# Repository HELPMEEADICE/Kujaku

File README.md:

# Kujaku（孔雀）

Kujaku 是一套用于孔雀造型灯光装置的开源硬件与固件设计，包含多路 PWM 主控板、3S 18650 电池与充电板、外壳模型和 ESP32-C3 固件。仓库中的历史文件沿用 Peacock 命名。

## 项目内容

- [主板 V2.1](PeacockMainV2_1/PeacockMainV2_1-Design.md)：KiCad 原理图、PCB、制造文件与设计记录，提供 12 路 PWM 和电流采样。
- [电池板 A2](PeacockBattery/A2/PeacockBattery-Design.md)：3S 电池、充电与握把接口设计，包含制造资料。
- [ESP32-C3 固件](firmware/peacock-esp32c3/README.md)：Rust 固件，包含灯效、音频、BLE 和电源管理；编译、烧录及接口说明见其 README。
- [外壳](PeacockEnclosure/)与[装配效果图](renders/)：DWG、STL、模型导出和渲染图。
- [主板 V2](PeacockMainV2/PeacockMainV2-Design.md)、[电池板 A1](PeacockBattery/PeacockBattery-Design.md)及仓库根目录的 KiCad 工程为历史版本，请按相应版本的文档使用。

## 开始使用

使用 KiCad 10 打开相应目录中的 `.kicad_pro`，并参考各设计记录中的接口、物料和制造说明。外壳模型位于 `PeacockEnclosure/`。固件的工具链、构建和烧录步骤详见[固件说明](firmware/peacock-esp32c3/README.md)。

**项目仍需实物验证。** ERC/DRC 结果不代表整机通过验证；电池接触、充放电保护、温升、装壳及接口兼容性等须按对应版本的设计记录完成验证。固件中的 PY32 采样从机协议仍是提案，仓库未提供该从机固件。制作或上电前请先阅读相关设计记录。

## 许可

本项目原创固件和其他软件代码采用 [GNU Affero General Public License v3.0](LICENSE)（AGPL-3.0-only）；原创硬件设计、外壳、渲染图及文档采用 [Creative Commons Attribution-ShareAlike 4.0 International](LICENSE-CC-BY-SA-4.0)（CC BY-SA 4.0）。使用设计资料时请署名 Kujaku 项目及相关贡献者，并遵守相同方式共享要求。

第三方材料及依赖仍遵循各自的许可和声明；例如 ESP32 模型相关许可见 [Espressif 许可文件](PeacockMainV2_1/Espressif-LICENSE.md)。上述许可不改变第三方权利。

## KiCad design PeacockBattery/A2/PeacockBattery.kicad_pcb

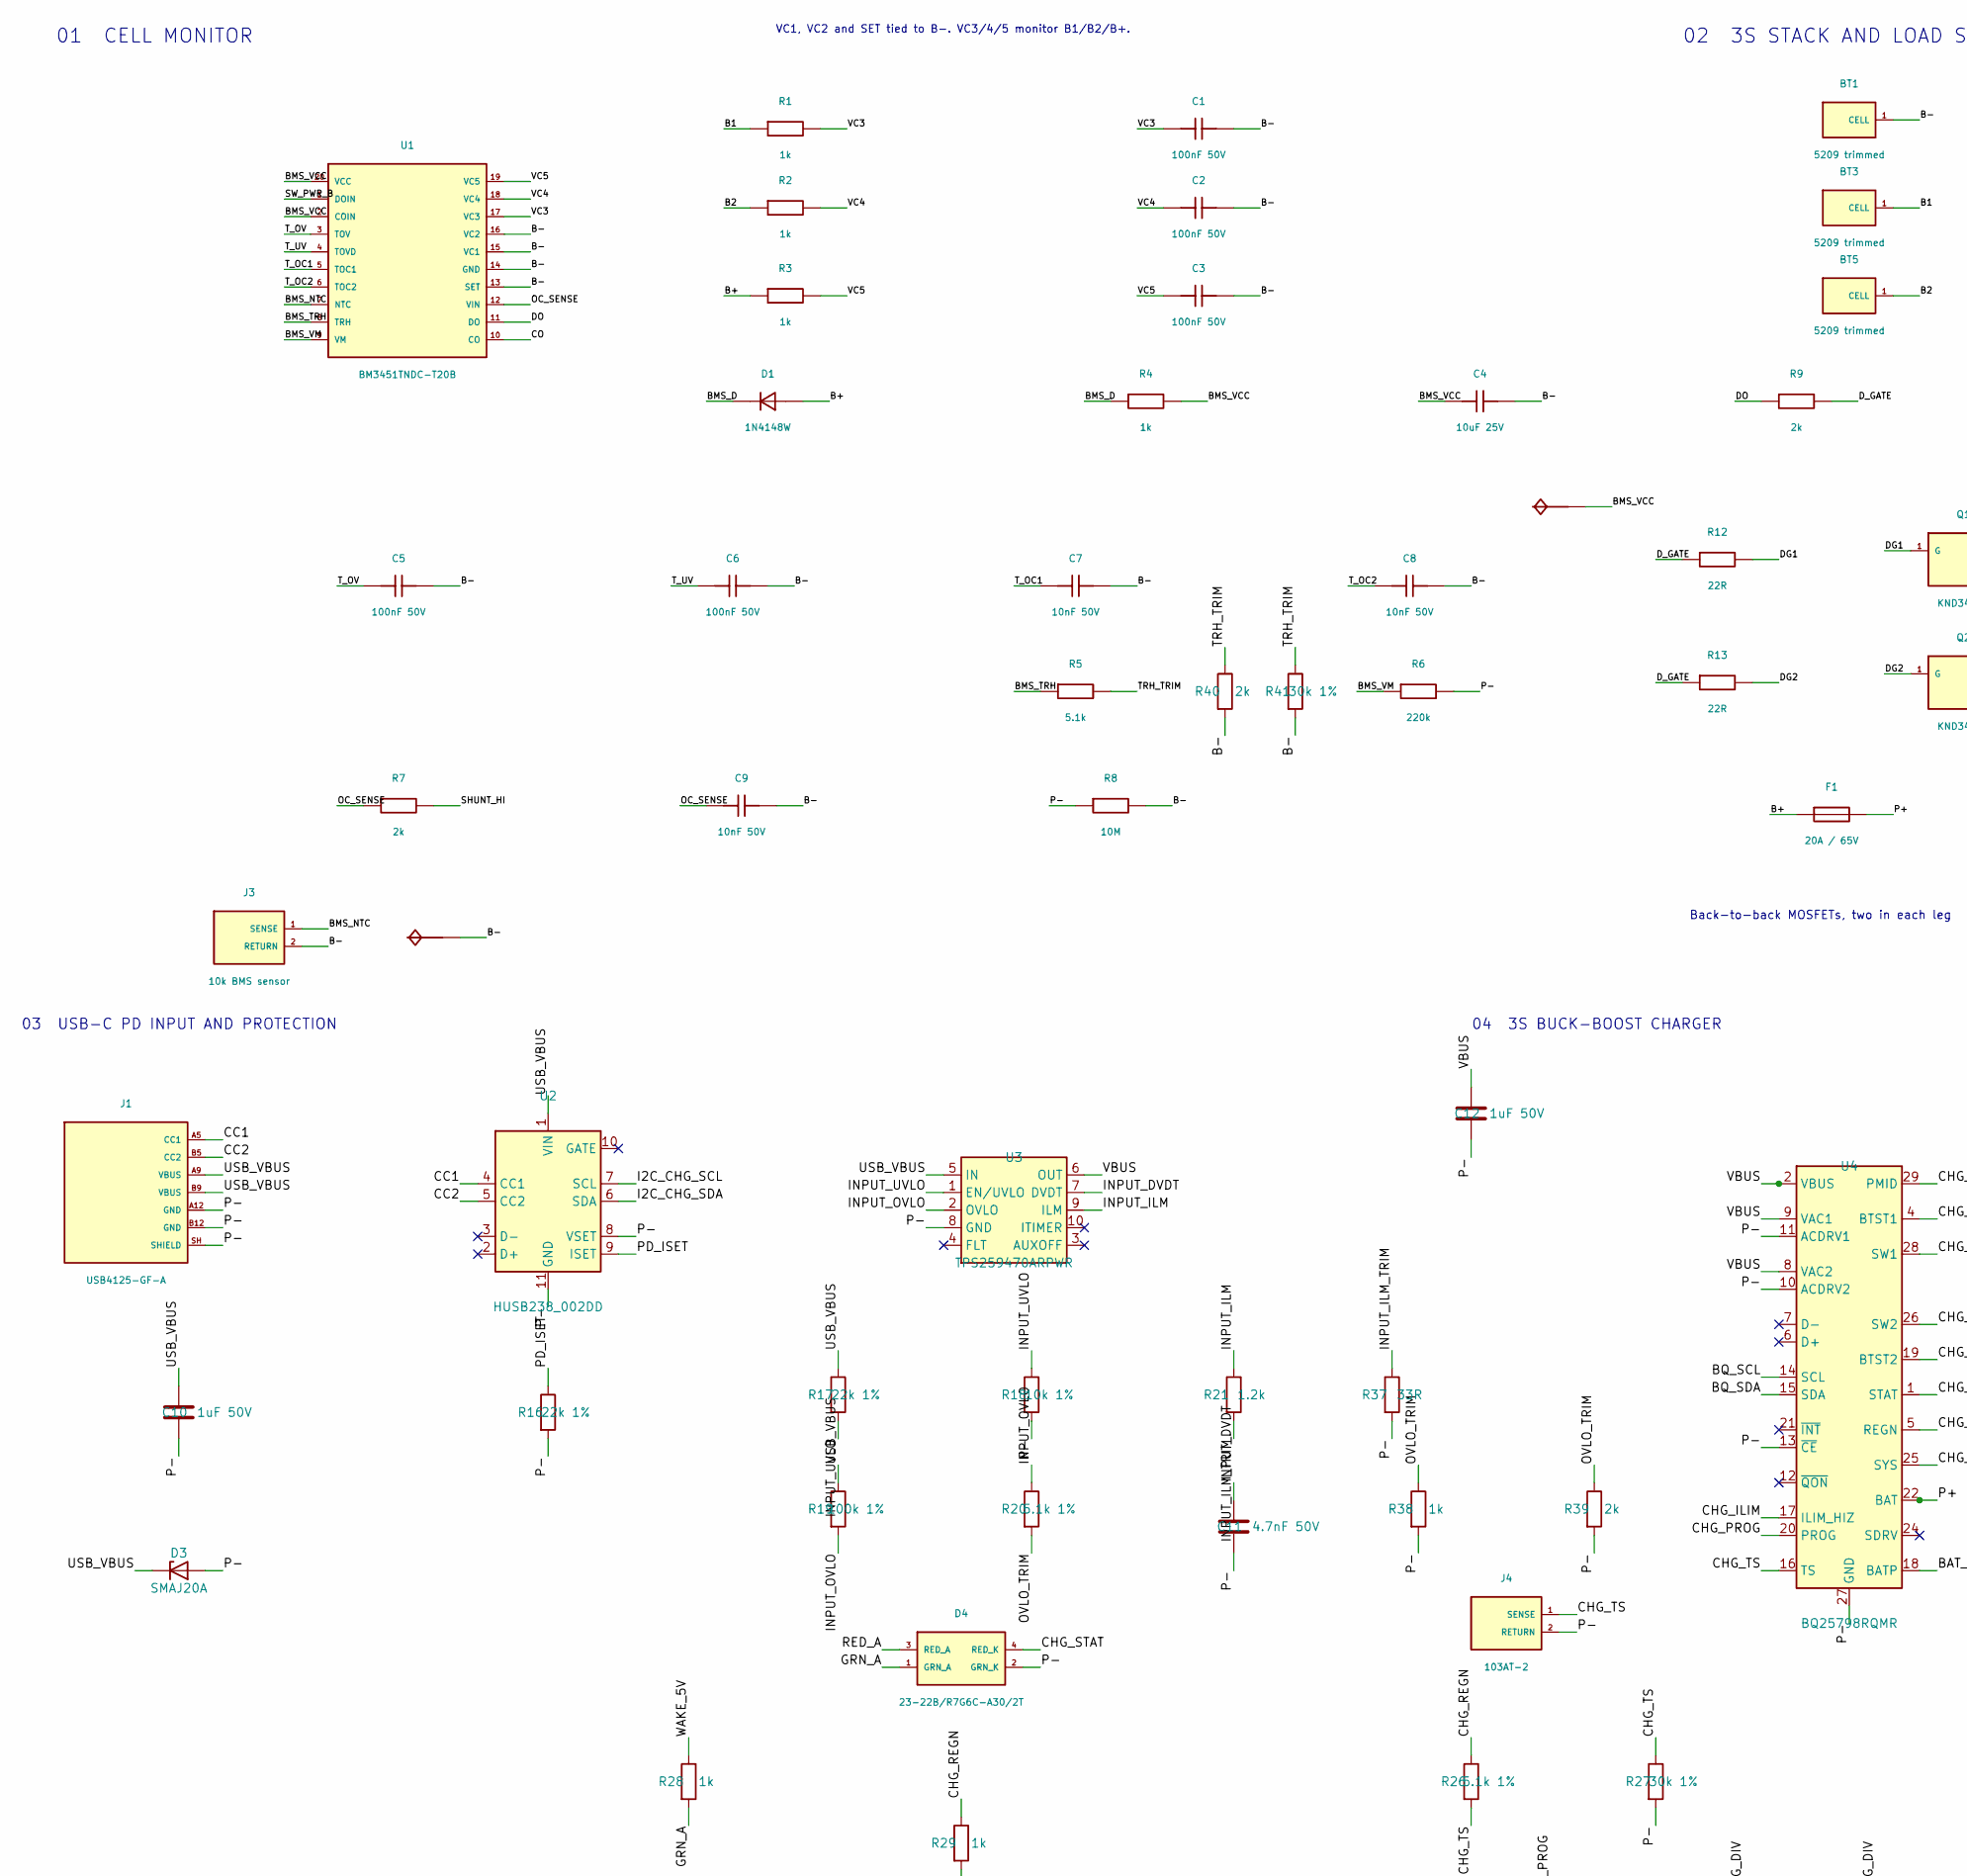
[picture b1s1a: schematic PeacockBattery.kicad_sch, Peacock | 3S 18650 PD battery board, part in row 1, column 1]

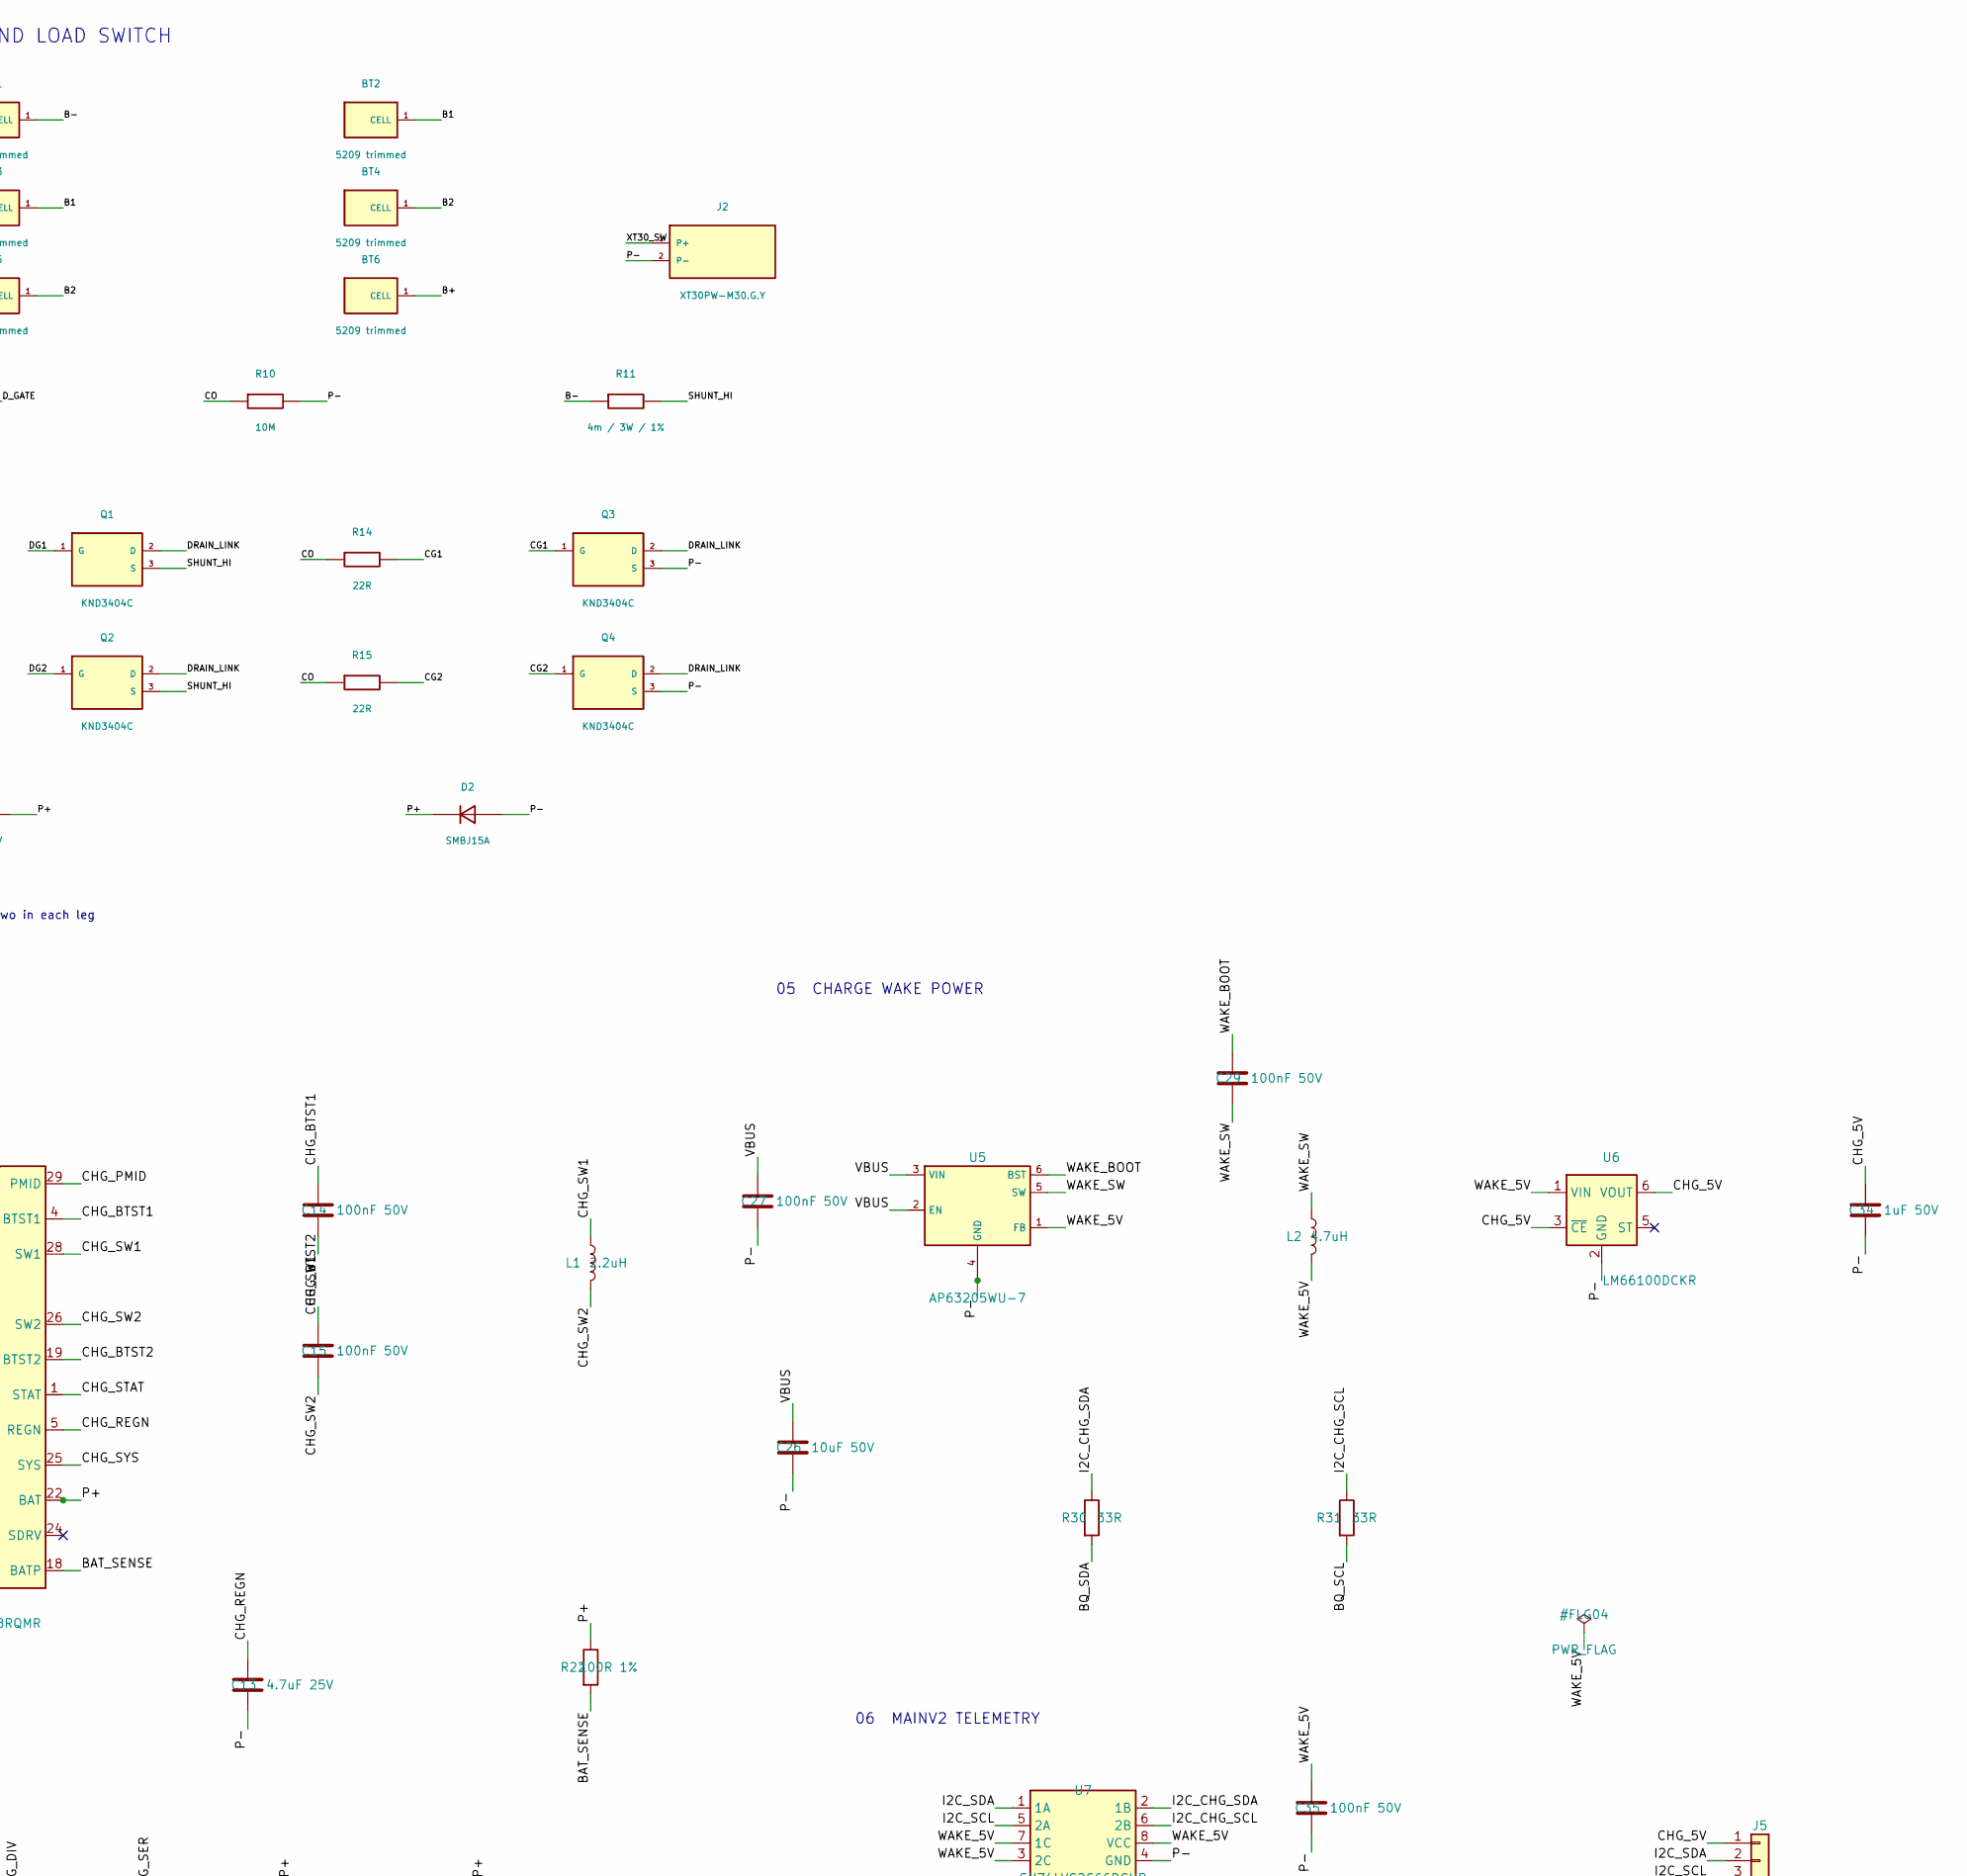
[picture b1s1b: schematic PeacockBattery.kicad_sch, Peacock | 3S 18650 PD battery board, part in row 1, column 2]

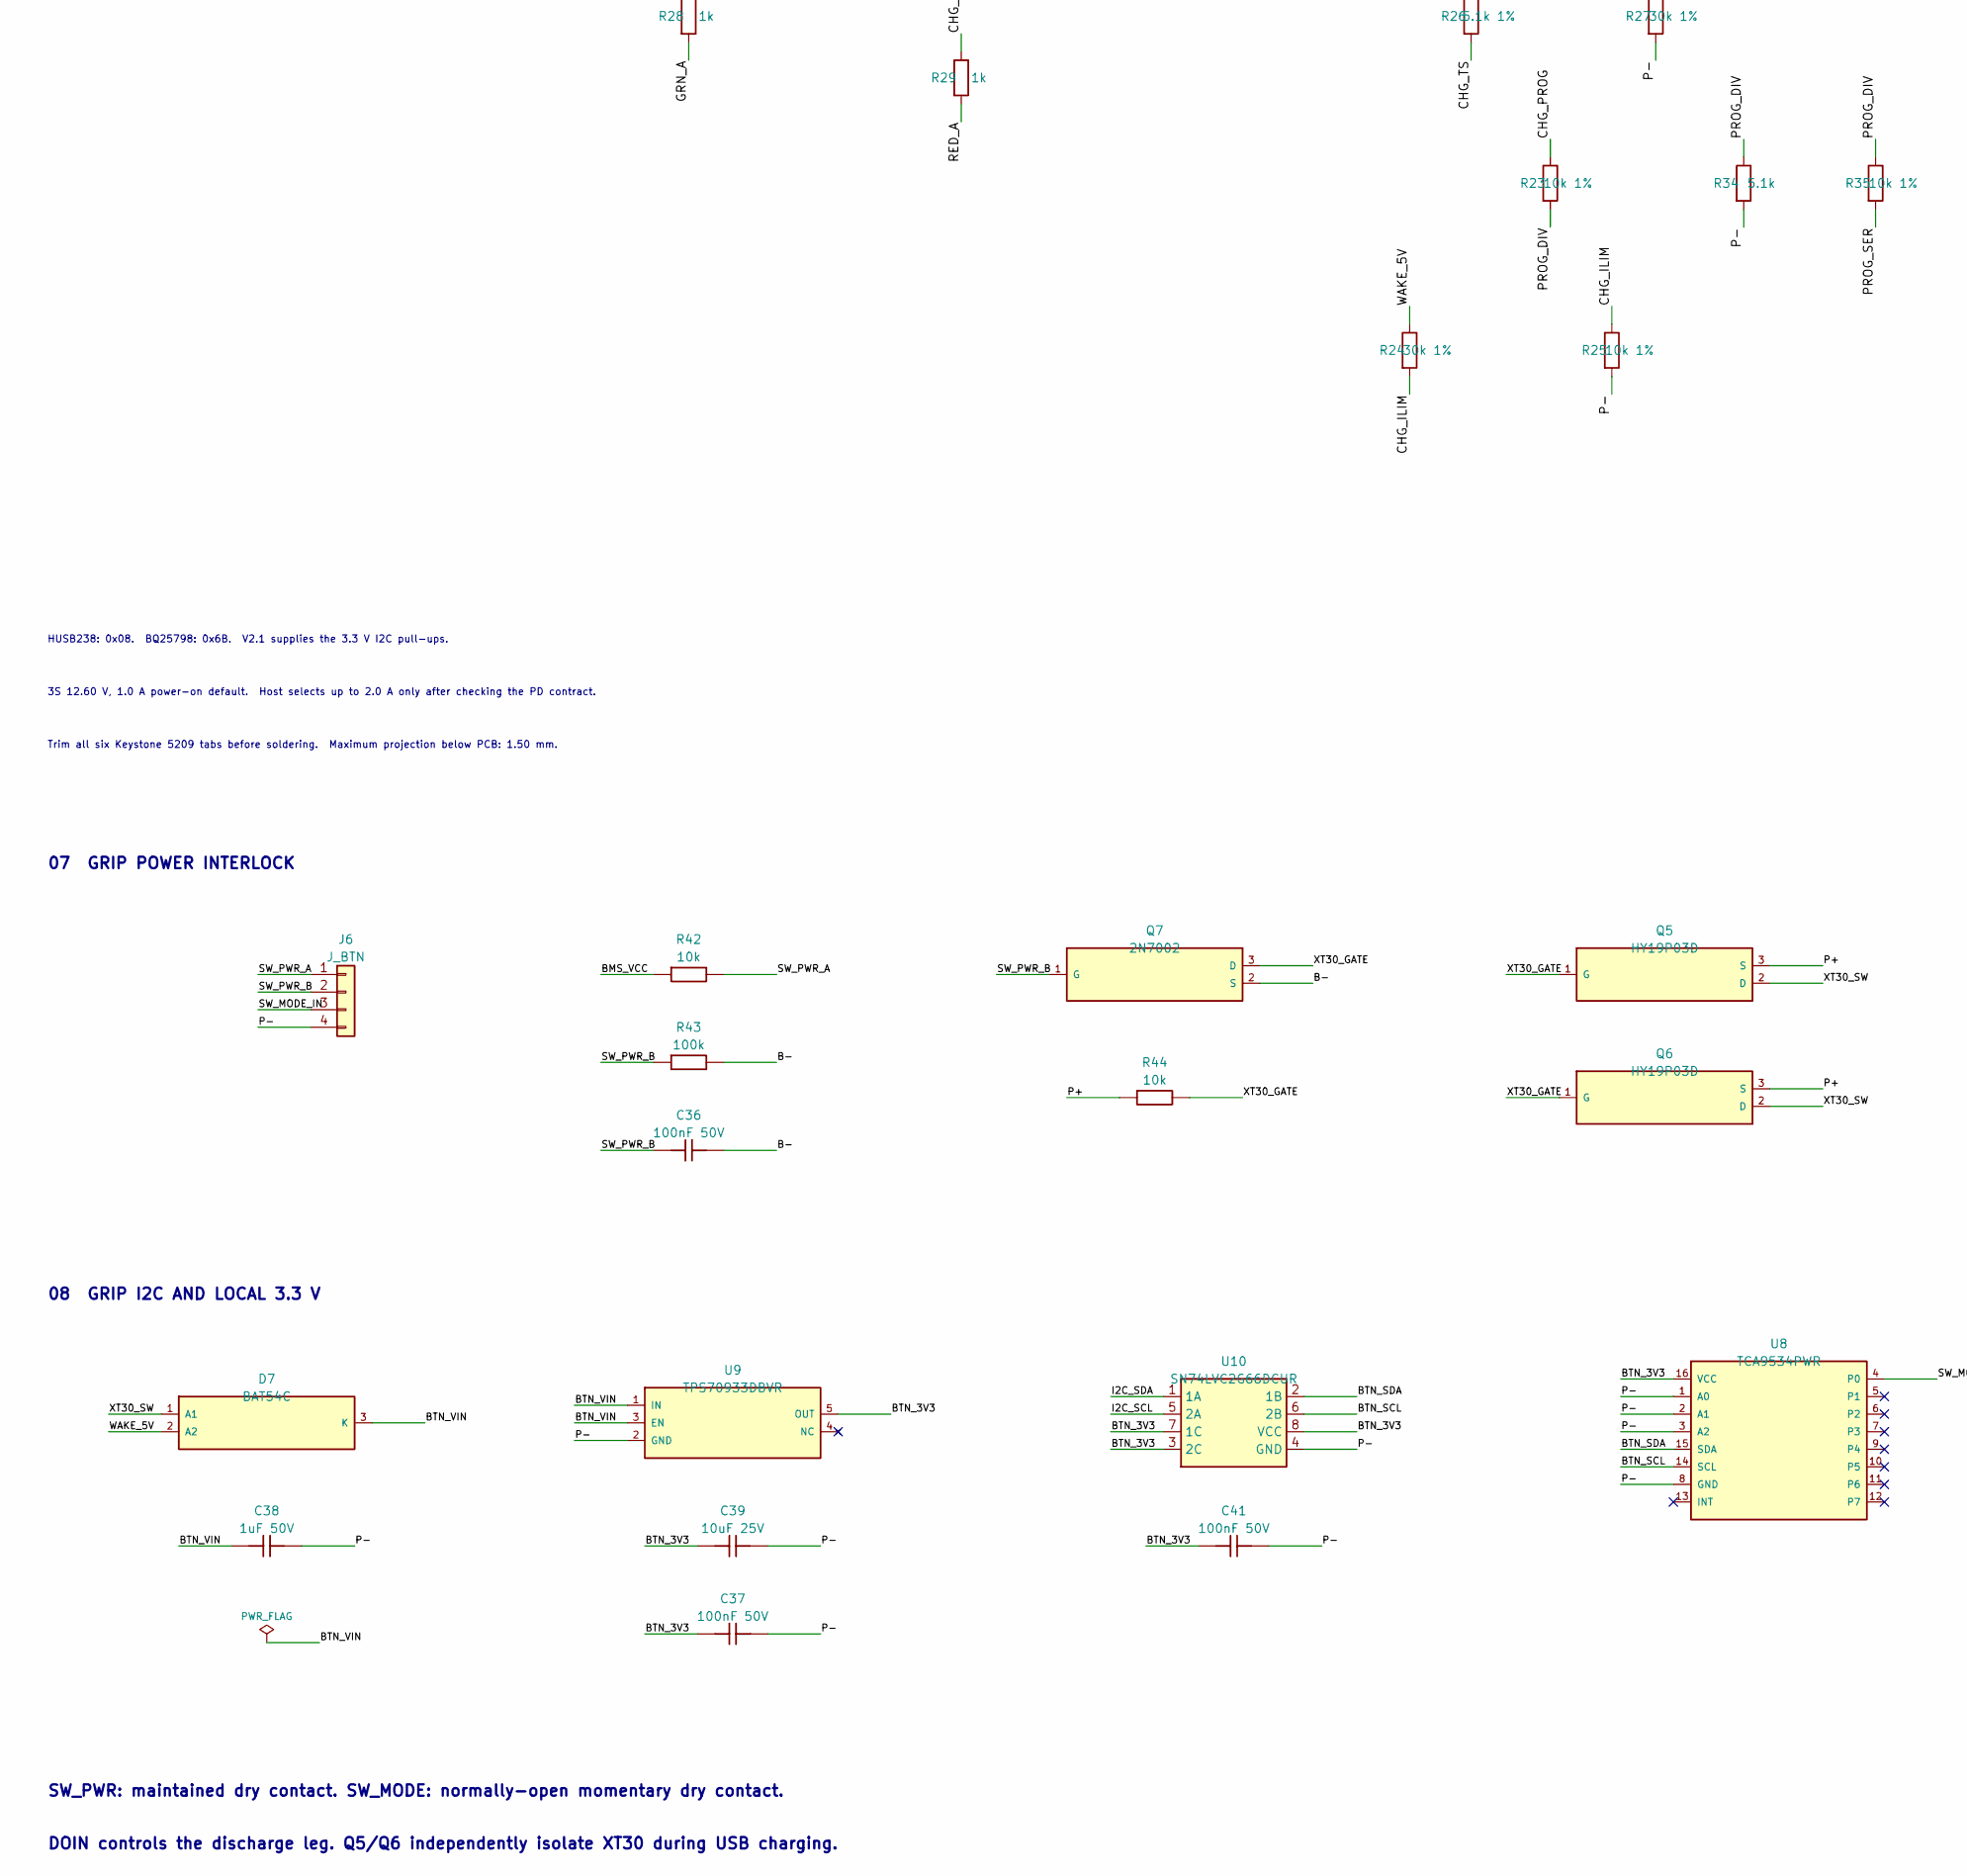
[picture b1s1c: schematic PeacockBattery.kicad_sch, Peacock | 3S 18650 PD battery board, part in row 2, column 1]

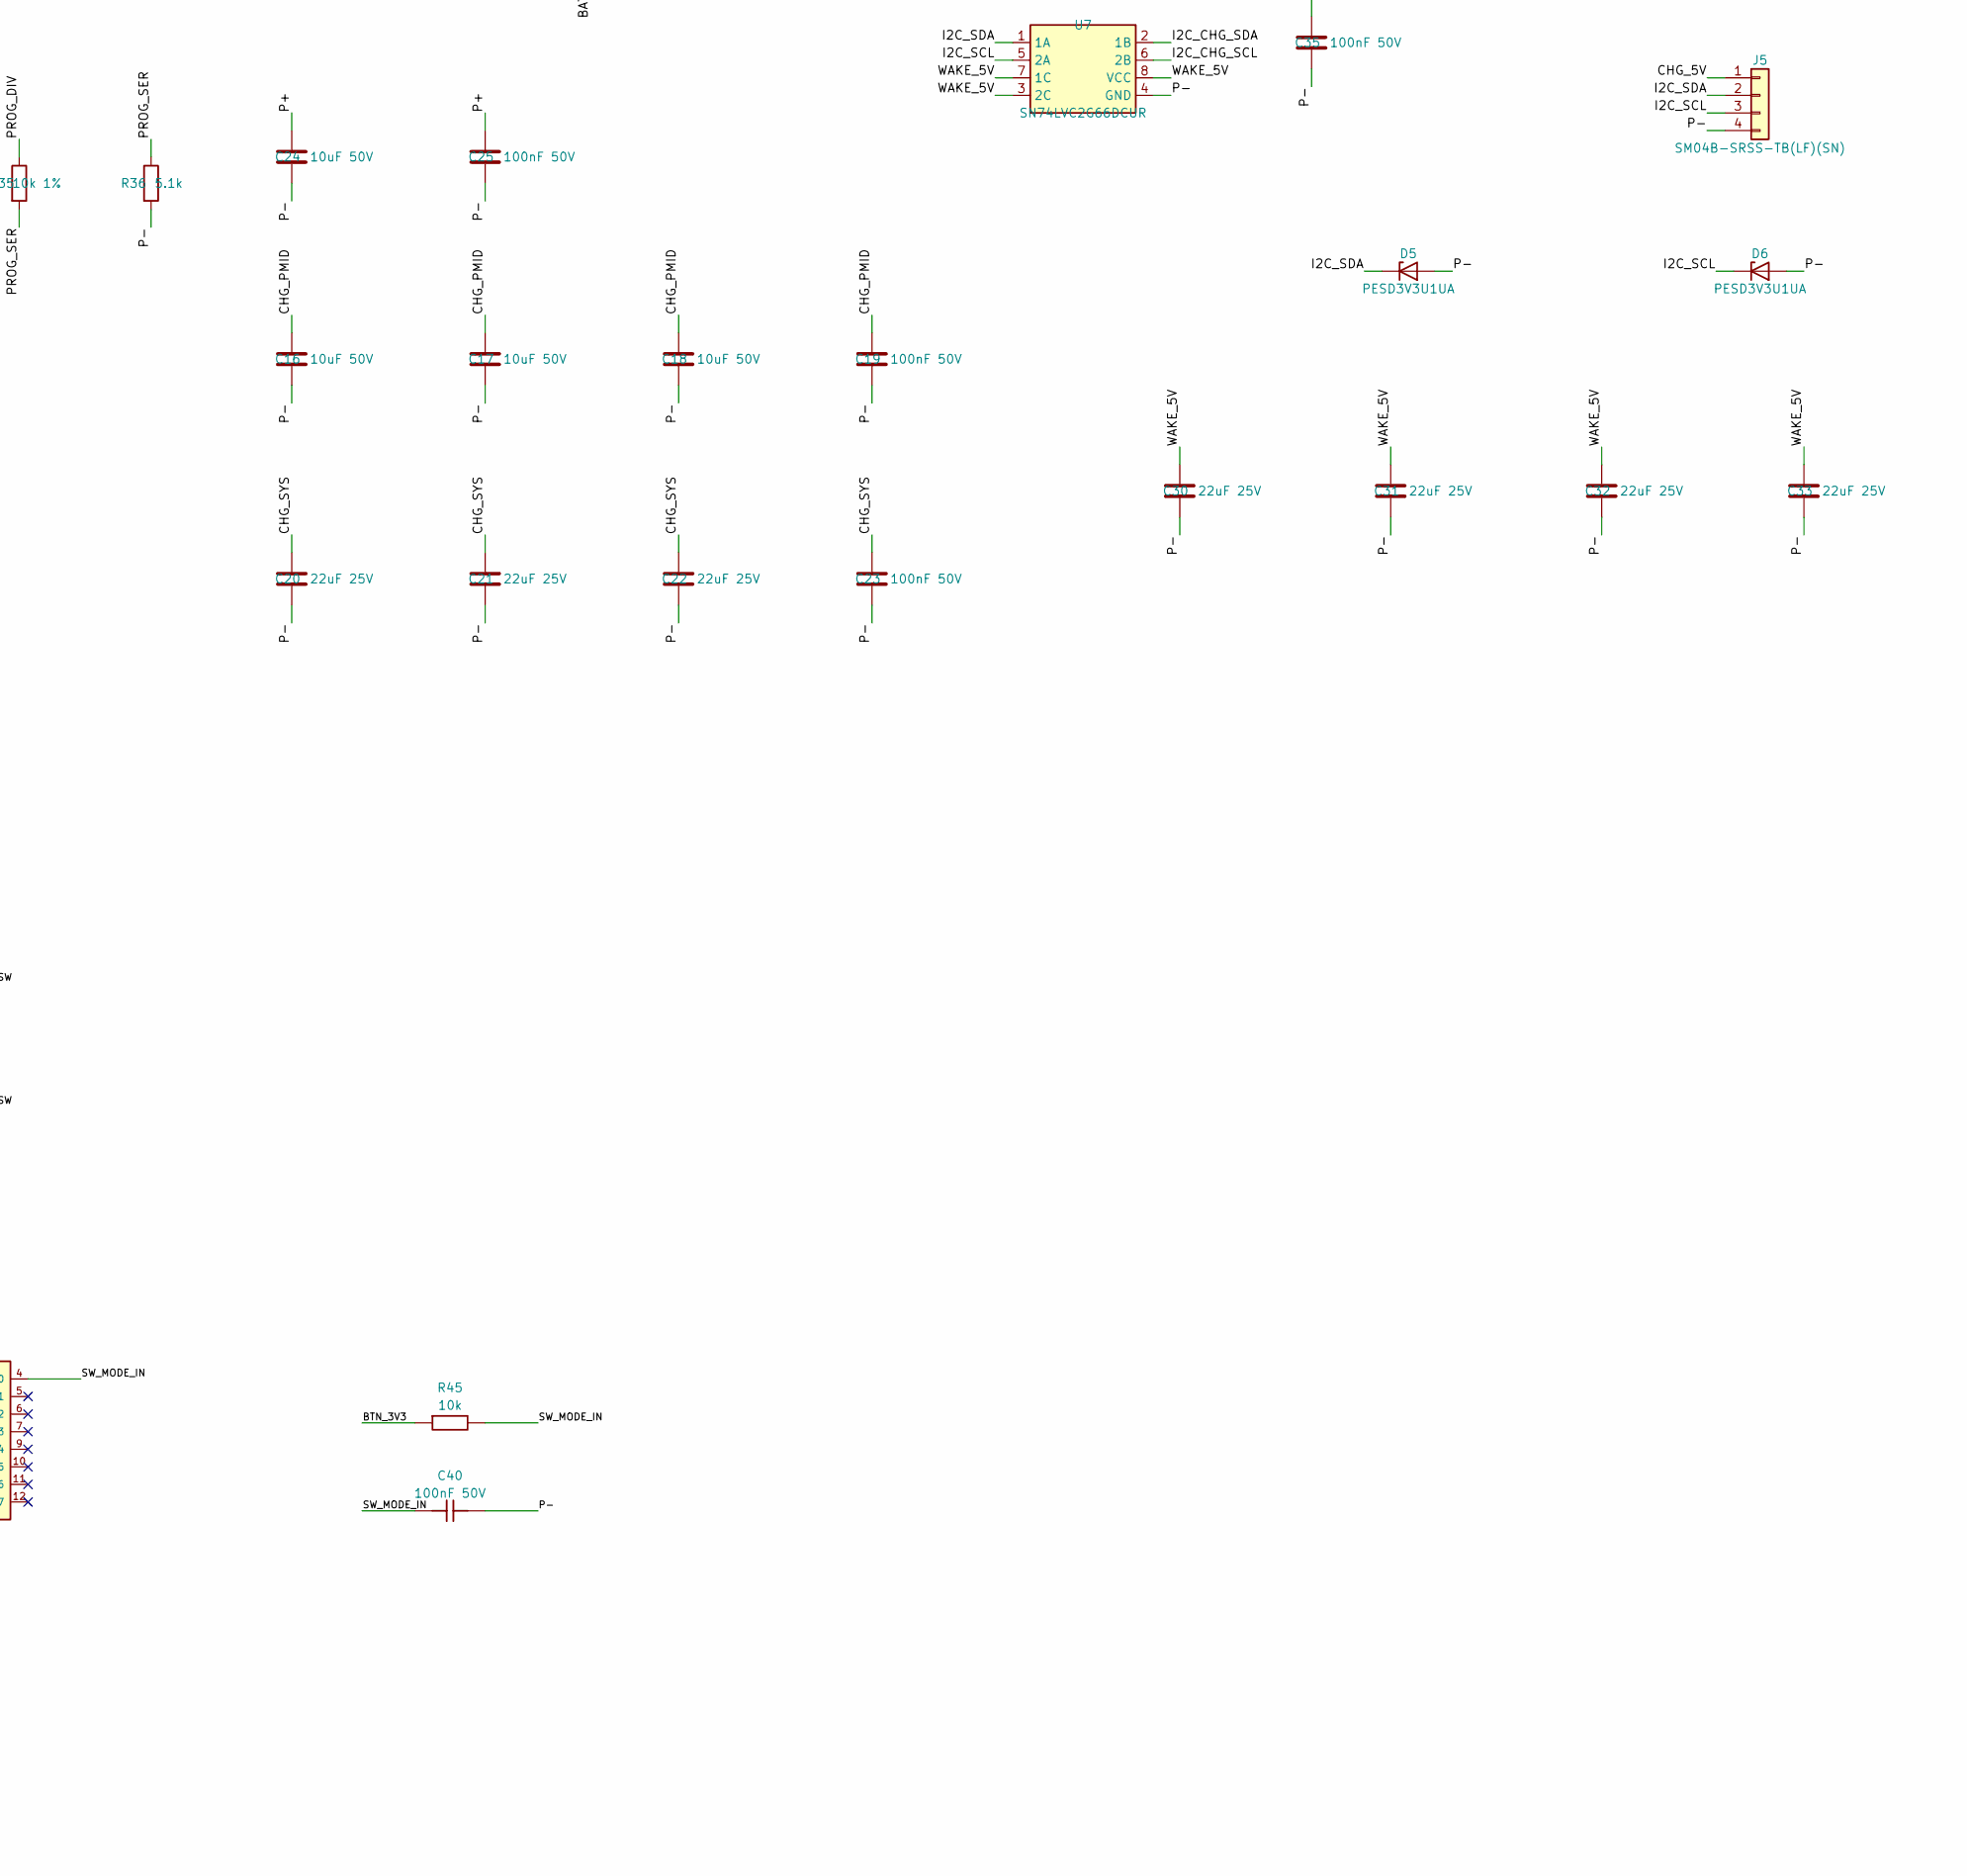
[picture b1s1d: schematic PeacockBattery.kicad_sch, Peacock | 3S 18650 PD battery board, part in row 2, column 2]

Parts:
BT1, BT2, BT3, BT4, BT5, BT6: 5209 trimmed; Keystone_5209_Trimmed; MPN TBD
C1, C2, C3, C5, C6, C14, C15, C19, C23, C25, C27, C29, C35, C36, C37, C40, C41: 100nF 50V; C_0603_1608Metric; MPN CC0603KRX7R9BB104; LCSC C14663
C4, C39: 10uF 25V; C_0805_2012Metric; MPN CL21A106KAYNNNE; LCSC C15850
C7, C8, C9: 10nF 50V; C_0603_1608Metric; MPN 0603B103K500NT; LCSC C57112
C10, C12, C34, C38: 1uF 50V; C_0603_1608Metric; MPN CL10A105KB8NNNC; LCSC C15849
C11: 4.7nF 50V; C_0603_1608Metric; MPN 0603B472K500NT; LCSC C53987
C13: 4.7uF 25V; C_0805_2012Metric; MPN CL21A475KAQNNNE; LCSC C1779
C16, C17, C18, C24, C26: 10uF 50V; C_1206_3216Metric; MPN CL31A106KBHNNNE; LCSC C13585
C20, C21, C22: 22uF 25V; C_1206_3216Metric; MPN CL31A226KAHNNNE; LCSC C12891
C30, C31, C32, C33: 22uF 25V; C_0805_2012Metric; MPN CL21A226MAQNNNE; LCSC C45783
D1: 1N4148W; D_SOD-123; MPN 1N4148W; LCSC C81598
D2: SMBJ15A; D_SMB; MPN SMBJ15A; LCSC C19077569
D3: SMAJ20A; D_SMA; MPN SMAJ20A; LCSC C41376408
D4: 23-22B/R7G6C-A30/2T; LED_Everlight_23-22B_Reverse; MPN 23-22B/R7G6C-A30/2T; LCSC C424084
D5, D6: PESD3V3U1UA; D_SOD-323; MPN PESD3V3U1UA,115; LCSC C403915
D7: BAT54C; SOT-23; MPN BAT54C; LCSC C2135
F1: 20A / 65V; Fuse_Littelfuse-NANO2-451_453; MPN 0451020.MRL; LCSC C178980
J1: USB4125-GF-A; USB4125_HandAssembly; MPN USB4125-GF-A; LCSC C3151650
J2: XT30PW-M30.G.Y; XT30PW-M_Edge; MPN XT30PW-M30.G.Y; LCSC C431092
J3: 10k BMS sensor; SolderWire-0.15sqmm_1x02_P4mm_D0.5mm_OD1.5mm; MPN 10k NTC, insulated leads
J4: 103AT-2; SolderWire-0.15sqmm_1x02_P4mm_D0.5mm_OD1.5mm; MPN 103AT-2
J5: SM04B-SRSS-TB(LF)(SN); JST_SH_SM04B_HandAssembly; MPN SM04B-SRSS-TB(LF)(SN); LCSC C160404
J6: J_BTN; Grip_1x04_SolderPads; MPN Wire-to-pad; LCSC N/A
L1: 2.2uH; L_APV_APH0530C; MPN APH0530C-2R2M-TCD5; LCSC C50326270
L2: 4.7uH; L_YJYCOIN_YSPI0730; MPN YSPI0730-4R7M; LCSC C351117
Q1, Q2, Q3, Q4: KND3404C; TO-252-2; MPN KND3404C; LCSC C455981
Q5, Q6: HY19P03D; TO-252-2; MPN HY19P03D; LCSC C122492
Q7: 2N7002; SOT-23; MPN 2N7002; LCSC C8545
R1, R2, R3, R4, R28, R29, R38: 1k; R_0603_1608Metric; MPN 0603WAF1001T5E; LCSC C21190
R5, R34, R36: 5.1k; R_0603_1608Metric; MPN 0603WAF5101T5E; LCSC C23186
R6: 220k; R_0603_1608Metric; MPN 0603WAF2203T5E; LCSC C22961
R7, R9, R39, R40: 2k; R_0603_1608Metric; MPN 0603WAF2001T5E; LCSC C22975
R8, R10: 10M; R_0603_1608Metric; MPN 0603WAF1005T5E; LCSC C7250
R11: 4m / 3W / 1%; WSLP2512_4m; MPN WSLP25124L000FEA; LCSC C2091033
R12, R13, R14, R15: 22R; R_0603_1608Metric; MPN 0603WAF220JT5E; LCSC C23345
R16, R17: 22k 1%; R_0603_1608Metric; MPN 0603WAF2202T5E; LCSC C31850
R18, R23, R25, R35: 10k 1%; R_0603_1608Metric; MPN 0603WAF1002T5E; LCSC C25804
R19: 100k 1%; R_0603_1608Metric; MPN 0603WAF1003T5E; LCSC C25803
R20, R26: 5.1k 1%; R_0603_1608Metric; MPN 0603WAF5101T5E; LCSC C23186
R21: 1.2k; R_0603_1608Metric; MPN 0603WAF1201T5E; LCSC C22765
R22: 100R 1%; R_0603_1608Metric; MPN 0603WAF1000T5E; LCSC C22775
R24, R27, R41: 30k 1%; R_0603_1608Metric; MPN 0603WAF3002T5E; LCSC C22984
R30, R31, R37: 33R; R_0603_1608Metric; MPN 0603WAF330JT5E; LCSC C23140
R42, R44, R45: 10k; R_0603_1608Metric; MPN 0603WAF1002T5E; LCSC C25804
R43: 100k; R_0603_1608Metric; MPN 0603WAF1003T5E; LCSC C25803
U1: BM3451TNDC-T20B; TSSOP-20_4.4x6.5mm_P0.65mm; MPN BM3451TNDC-T20B; LCSC C2686222
U2: HUSB238_002DD; WDFN-10-1EP_3x3mm_P0.5mm_EP1.8x2.5mm; MPN HUSB238_002DD; LCSC C7471904
U3: TPS259470ARPWR; TI_RPW0010A; MPN TPS259470ARPWR; LCSC C3662799
U4: BQ25798RQMR; Texas_RQM0029A_VQFN-29_4x4mm_P0.4mm; MPN BQ25798RQMR; LCSC C2876593
U5: AP63205WU-7; TSOT-23-6; MPN AP63205WU-7; LCSC C2071056
U6: LM66100DCKR; SOT-363_SC-70-6; MPN LM66100DCKR; LCSC C2869734
U7, U10: SN74LVC2G66DCUR; VSSOP-8_2.3x2mm_P0.5mm; MPN SN74LVC2G66DCUR; LCSC C181970
U8: TCA9534PWR; TSSOP-16_4.4x5mm_P0.65mm; MPN TCA9534PWR; LCSC C783615
U9: TPS70933DBVR; SOT-23-5; MPN TPS70933DBVR; LCSC C89347

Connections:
/B1: BT2.1, BT3.1, R1.1
/B2: BT4.1, BT5.1, R2.1
/B+: BT6.1, D1.2, F1.1, R3.1
/B-: BT1.1, C1.2, C2.2, C3.2, C4.2, C5.2, C6.2, C7.2, C8.2, C9.2, C36.2, J3.2 (RETURN), Q7.2 (S), R8.2, R11.1, R40.2, R41.2, R43.2, U1.13 (SET), U1.14 (GND), U1.15 (VC1), U1.16 (VC2)
/BAT_SENSE: R22.2, U4.18 (BATP)
/BMS_D: D1.1, R4.1
/BMS_NTC: J3.1 (SENSE), U1.7 (NTC)
/BMS_TRH: R5.1, U1.8 (TRH)
/BMS_VCC: C4.1, R4.2, R42.1, U1.2 (COIN), U1.20 (VCC)
/BMS_VM: R6.1, U1.9 (VM)
/BQ_SCL: R31.2, U4.14 (SCL)
/BQ_SDA: R30.2, U4.15 (SDA)
/BTN_3V3: C37.1, C39.1, C41.1, R45.1, U8.16 (VCC), U9.5 (OUT), U10.3 (2C), U10.7 (1C), U10.8 (VCC)
/BTN_SCL: U8.14 (SCL), U10.6 (2B)
/BTN_SDA: U8.15 (SDA), U10.2 (1B)
/BTN_VIN: C38.1, D7.3 (K), U9.1 (IN), U9.3 (EN)
/CC1: J1.A5 (CC1), U2.4 (CC1)
/CC2: J1.B5 (CC2), U2.5 (CC2)
/CG1: Q3.1 (G), R14.2
/CG2: Q4.1 (G), R15.2
/CHG_5V: C34.1, J5.1, U6.3 (~CE), U6.6 (VOUT)
/CHG_BTST1: C14.1, U4.4 (BTST1)
/CHG_BTST2: C15.1, U4.19 (BTST2)
/CHG_ILIM: R24.2, R25.1, U4.17 (ILIM_HIZ)
/CHG_PMID: C16.1, C17.1, C18.1, C19.1, U4.29 (PMID)
/CHG_PROG: R23.1, U4.20 (PROG)
/CHG_REGN: C13.1, R26.1, R29.1, U4.5 (REGN)
/CHG_STAT: D4.4 (RED_K), U4.1 (STAT)
/CHG_SW1: C14.2, L1.1, U4.28 (SW1)
/CHG_SW2: C15.2, L1.2, U4.26 (SW2)
/CHG_SYS: C20.1, C21.1, C22.1, C23.1, U4.25 (SYS)
/CHG_TS: J4.1 (SENSE), R26.2, R27.1, U4.16 (TS)
/CO: R10.1, R14.1, R15.1, U1.10 (CO)
/DG1: Q1.1 (G), R12.2
/DG2: Q2.1 (G), R13.2
/DO: R9.1, U1.11 (DO)
/DRAIN_LINK: Q1.2 (D), Q2.2 (D), Q3.2 (D), Q4.2 (D)
/D_GATE: R9.2, R12.1, R13.1
/GRN_A: D4.1 (GRN_A), R28.2
/I2C_CHG_SCL: R31.1, U2.7 (SCL), U7.6 (2B)
/I2C_CHG_SDA: R30.1, U2.6 (SDA), U7.2 (1B)
/I2C_SCL: D6.1 (K), J5.3, U7.5 (2A), U10.5 (2A)
/I2C_SDA: D5.1 (K), J5.2, U7.1 (1A), U10.1 (1A)
/INPUT_DVDT: C11.1, U3.7 (DVDT)
/INPUT_ILM: R21.1, U3.9 (ILM)
/INPUT_ILM_TRIM: R21.2, R37.1
/INPUT_OVLO: R19.2, R20.1, U3.2 (OVLO)
/INPUT_UVLO: R17.2, R18.1, U3.1 (EN/UVLO)
/OC_SENSE: C9.1, R7.1, U1.12 (VIN)
/OVLO_TRIM: R20.2, R38.1, R39.1
/P+: C24.1, C25.1, D2.1, F1.2, Q5.3 (S), Q6.3 (S), R22.1, R44.1, U4.22 (BAT), U4.23 (BAT)
/P-: C10.2, C11.2, C12.2, C13.2, C16.2, C17.2, C18.2, C19.2, C20.2, C21.2, C22.2, C23.2, C24.2, C25.2, C26.2, C27.2, C30.2, C31.2, C32.2, C33.2, C34.2, C35.2, C37.2, C38.2, C39.2, C40.2, C41.2, D2.2, D3.2 (A), D4.2 (GRN_K), D5.2 (A), D6.2 (A), J1.A12 (GND), J1.B12 (GND), J1.SH (SHIELD), J2.2 (P-), J4.2 (RETURN), J5.4, J6.4, Q3.3 (S), Q4.3 (S), R6.2, R8.1, R10.2, R16.2, R18.2, R25.2, R27.2, R34.2, R36.2, R37.2, R38.2, R39.2, U2.8 (VSET), U2.11 (GND), U3.8 (GND), U4.10 (ACDRV2), U4.11 (ACDRV1), U4.13 (~CE), U4.27 (GND), U5.4 (GND), U6.2 (GND), U7.4 (GND), U8.1 (A0), U8.2 (A1), U8.3 (A2), U8.8 (GND), U9.2 (GND), U10.4 (GND)
/PD_ISET: R16.1, U2.9 (ISET)
/PROG_DIV: R23.2, R34.1, R35.1
/PROG_SER: R35.2, R36.1
/RED_A: D4.3 (RED_A), R29.2
/SHUNT_HI: Q1.3 (S), Q2.3 (S), R7.2, R11.2
/SW_MODE_IN: C40.1, J6.3, R45.2, U8.4 (P0)
/SW_PWR_A: J6.1, R42.2
/SW_PWR_B: C36.1, J6.2, Q7.1 (G), R43.1, U1.1 (DOIN)
/TRH_TRIM: R5.2, R40.1, R41.1
/T_OC1: C7.1, U1.5 (TOC1)
/T_OC2: C8.1, U1.6 (TOC2)
/T_OV: C5.1, U1.3 (TOV)
/T_UV: C6.1, U1.4 (TOVD)
/USB_VBUS: C10.1, D3.1 (K), J1.A9 (VBUS), J1.B9 (VBUS), R17.1, R19.1, U2.1 (VIN), U3.5 (IN)
/VBUS: C12.1, C26.1, C27.1, U3.6 (OUT), U4.2 (VBUS), U4.3 (VBUS), U4.8 (VAC2), U4.9 (VAC1), U5.2 (EN), U5.3 (VIN)
/VC3: C1.1, R1.2, U1.17 (VC3)
/VC4: C2.1, R2.2, U1.18 (VC4)
/VC5: C3.1, R3.2, U1.19 (VC5)
/WAKE_5V: C30.1, C31.1, C32.1, C33.1, C35.1, D7.2 (A2), L2.2, R24.1, R28.1, U5.1 (FB), U6.1 (VIN), U7.3 (2C), U7.7 (1C), U7.8 (VCC)
/WAKE_BOOT: C29.1, U5.6 (BST)
/WAKE_SW: C29.2, L2.1, U5.5 (SW)
/XT30_GATE: Q5.1 (G), Q6.1 (G), Q7.3 (D), R44.2
/XT30_SW: D7.1 (A1), J2.1 (P+), Q5.2 (D), Q6.2 (D)

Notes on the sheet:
01 CELL MONITOR
02 3S STACK AND LOAD SWITCH
VC1, VC2 and SET tied to B-. VC3/4/5 monitor B1/B2/B+.
Back-to-back MOSFETs, two in each leg
03 USB-C PD INPUT AND PROTECTION
04 3S BUCK-BOOST CHARGER
05 CHARGE WAKE POWER
06 MAINV2 TELEMETRY
HUSB238: 0x08. BQ25798: 0x6B. V2.1 supplies the 3.3 V I2C pull-ups.
3S 12.60 V, 1.0 A power-on default. Host selects up to 2.0 A only after checking the PD contract.
Trim all six Keystone 5209 tabs before soldering. Maximum projection below PCB: 1.50 mm.
07 GRIP POWER INTERLOCK
08 GRIP I2C AND LOCAL 3.3 V
SW_PWR: maintained dry contact. SW_MODE: normally-open momentary dry contact.
DOIN controls the discharge leg. Q5/Q6 independently isolate XT30 during USB charging.
